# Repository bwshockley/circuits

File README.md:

# circuits
Collection of various circuit designs

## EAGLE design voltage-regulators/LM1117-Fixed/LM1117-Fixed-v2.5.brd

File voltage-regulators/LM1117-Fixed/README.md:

#LM1117 Based Fixed Voltage Regulator#

The goal behind this particular voltage regulator was a low drop-out (LDO) fairly high current (800mAh) accurate voltage regulator.  The LM1117 is an improvement over the LM317.  For additional information on the LM1117, please see Texas Instrument's [LM1117 Datasheet](http://www.ti.com/lit/ds/symlink/lm1117-n.pdf).

The board is designed with a 2.54mm (.1") pitch for headers at the bottom.  It can be installed vertically with a 90deg header or horizontally with a straight header.

R1 and LED are optional - only if you want to have a visual indicator that the LM1117 is providing power.

LM1117 is in SOT-223 package.

C1 and C2 should be 10uF+ Tantalum Capacitors in 7343 (metric) package.  See additional requirements in the datasheet.

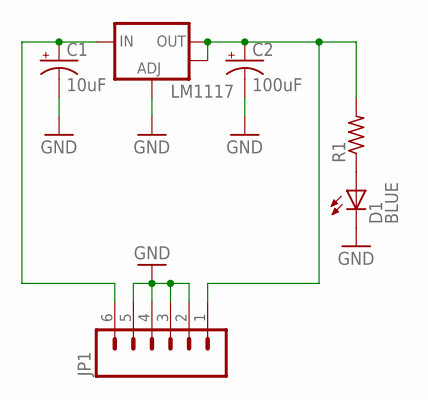
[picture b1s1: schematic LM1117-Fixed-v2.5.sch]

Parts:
C1: 10uF; CT7343
C2: 100uF; CT7343
D1: BLUE; CHIP-LED0805
JP1: M06NO_SILK_FEMALE_PTH; 1X06_NO_SILK
LM1117: V_REG_LM1117SOT223; SOT223
R1: R-US_R0805; R0805

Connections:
GND: C1.-, C2.-, D1.C, JP1.2, JP1.3, JP1.4, JP1.5, LM1117.1 (ADJ)
unnamed: C2.+, JP1.1, LM1117.2 (OUT), LM1117.4 (OUT), R1.2
unnamed: C1.+, JP1.6, LM1117.3 (IN)
unnamed: D1.A, R1.1

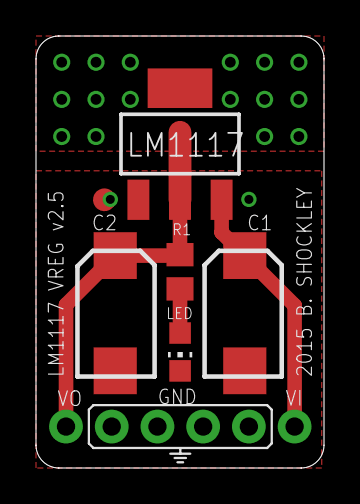
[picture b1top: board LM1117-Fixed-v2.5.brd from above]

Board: 2 copper layers, 16.0 x 24.0 mm, 6 parts (0 on the bottom side), 4 nets.

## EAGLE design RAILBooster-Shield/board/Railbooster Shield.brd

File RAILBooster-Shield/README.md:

#Railbooster Shield#

This design is based off of [RAILStars Railbooster](https://github.com/Railstars/RAILbooster).  It has been modified to fit onto an Arduino shield with a slightly different error check and control.

The shield should be good for DCC train control up to 12V and ~1.5Amps as is without heatsink.  Above that the LMD18200 will require some heatsink.  The voltage regulator is good as-is up to around 2Amps based off 15V input and 13V output.  The larger the deltaV between input and output voltage, the more likely a heatsink for the voltage regular will be required.  Please see the documentation on the voltage regulator.

The shield can provide voltage to the Arduino Uno R3 via the Vin pin of the Arduino.  It is fed off the shield voltage regulator.  In turn, the Arduino provides the 5V voltage for the shield's ATTINY, ICs, etc.

Adjust the output voltage of the voltage regulator with the adjustable resistor.

ATTINY44/84 can be programed via the Arudino UNO R3.

Design is provided as-is.  I cannot guarantee this will work and or not destroy your DCC trians.  Test the setup prior to powering the track.

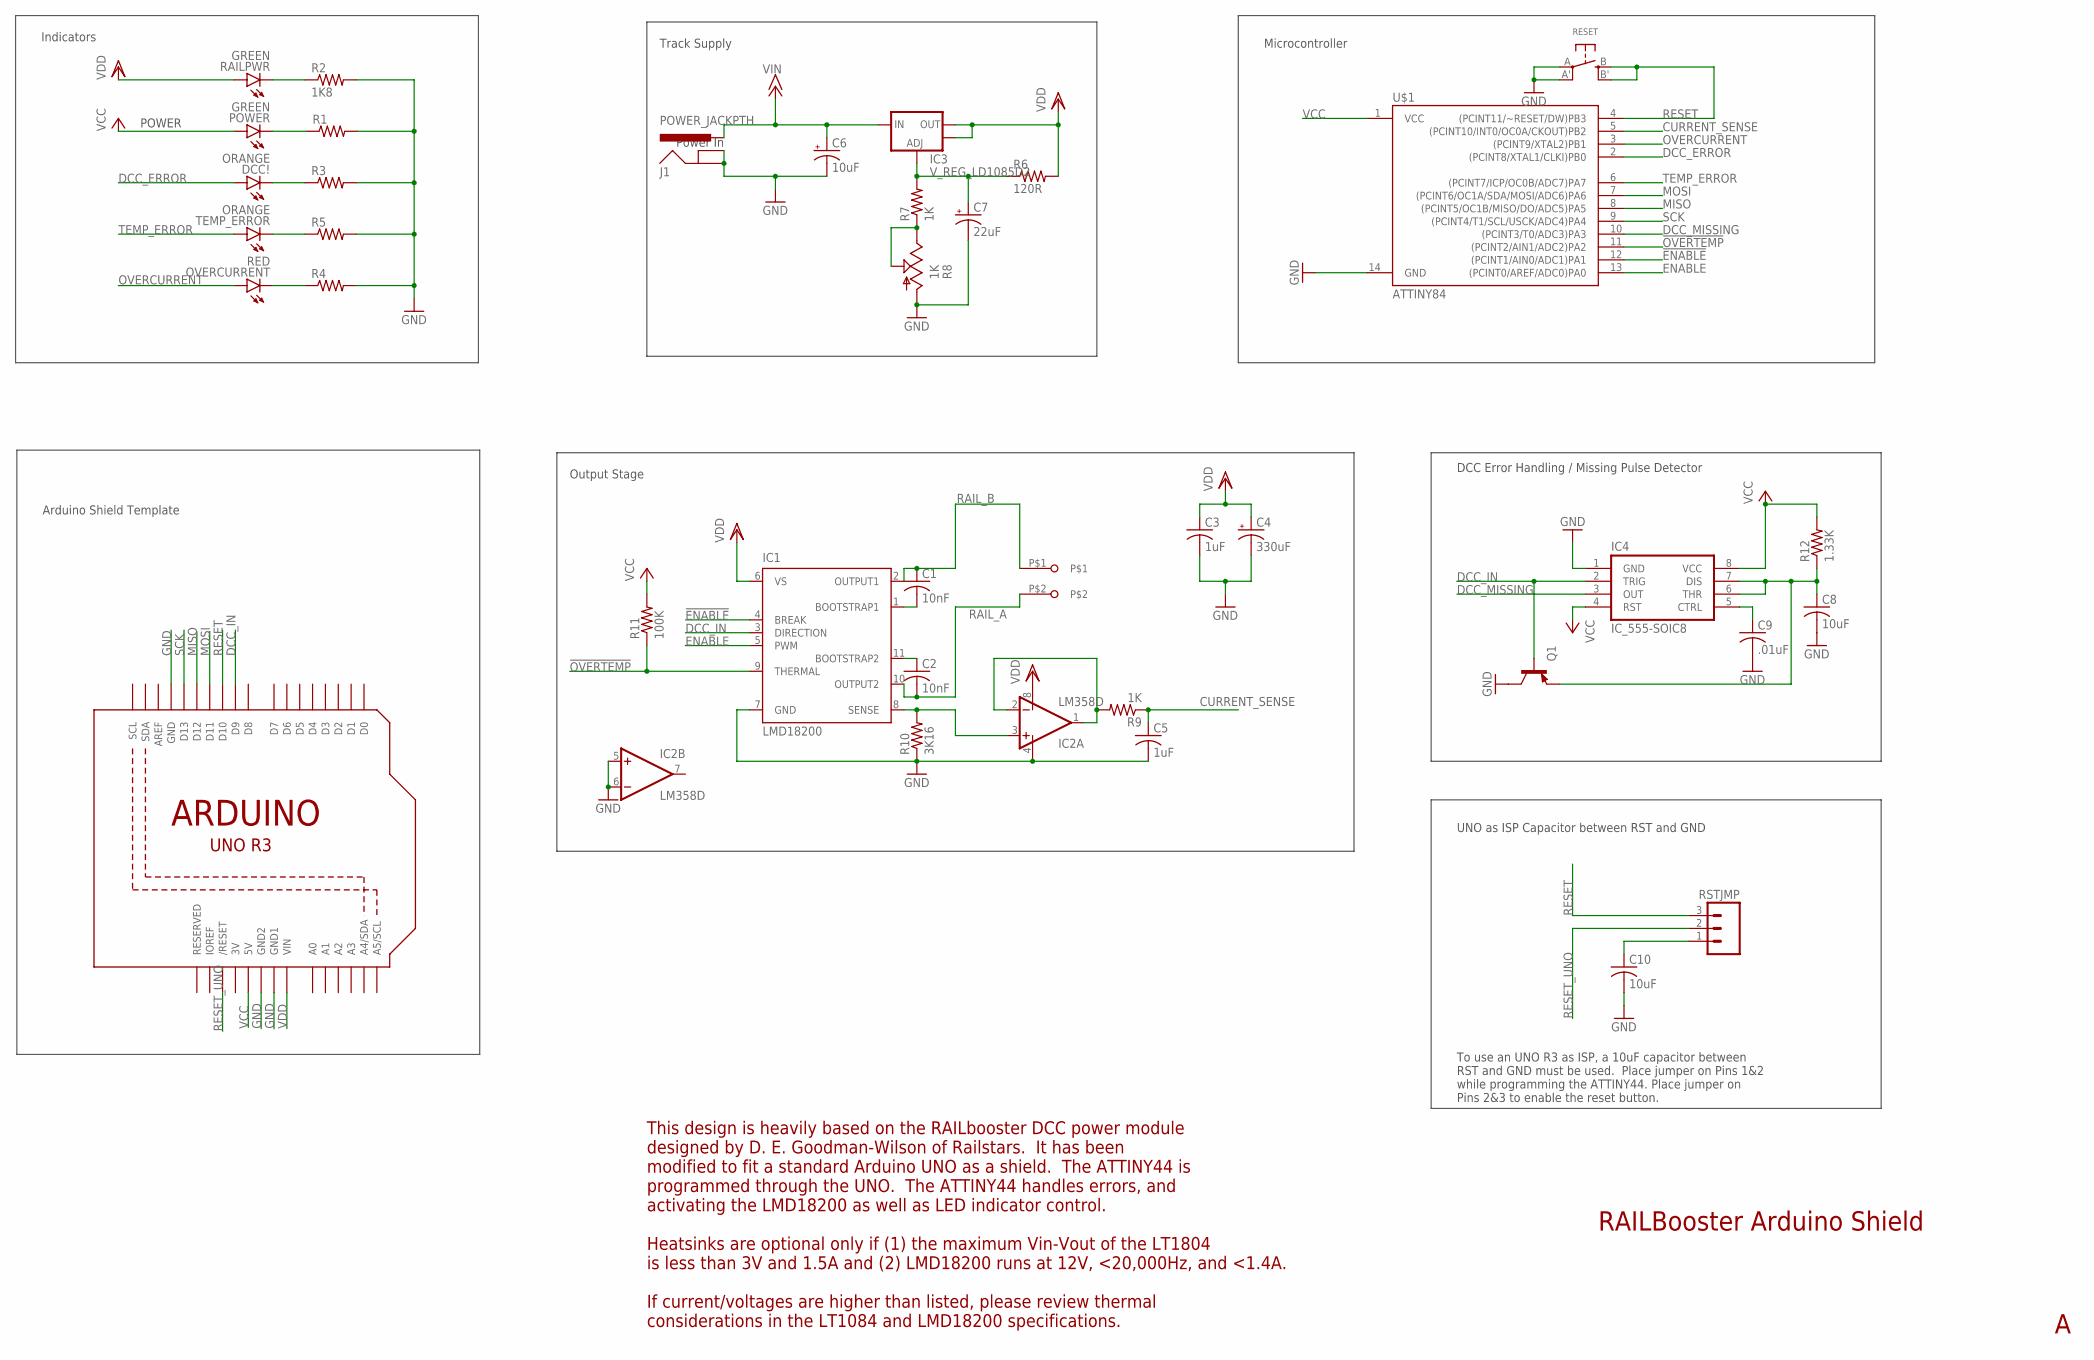
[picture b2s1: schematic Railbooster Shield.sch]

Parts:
C1, C2: 10nF; C1206
C3, C5: 1uF; C1206
C4: 330uF; E5-10,5
C6: 10uF; E2-5
C7: 22uF; E2-5
C8, C10: 10uF; C1206
C9: .01uF; C1206
DCC!: ORANGE; LED-1206
IC1: LMD18200; TO-220-11
IC2: LM358D; SO08
IC3: V_REG_LD1085D2; D2PACK/A
IC4: IC_555-SOIC8; SOIC-8
J1: POWER_JACKPTH; POWER_JACK_PTH
OVERCURRENT: RED; LED-1206
POWER: GREEN; LED-1206
Q1: TRANSISTOR_BJT_PNP-SOT-23-BCE; SOT-23
R1, R3, R4, R5: RESISTOR1206; 1206
R2: 1K8; 1206
R6: 120R; 1206
R7, R9: 1K; 1206
R8: 1K; S64W
R10: 3K16; 1206
R11: 100K; 1206
R12: 1.33K; 1206
RAILPWR: GREEN; LED-1206
RESET: SWITCH_TACT_SMT; EVQ-Q2
RSTJMP: M03PTH; 1X03
TEMP_ERROR: ORANGE; LED-1206
U1: ARDUINOR3-DIMENSION; ARDUINOR3
U$1: ATTINY84; SO14
X4: SCREWTERMINAL-5.08-2

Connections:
3V: U1.3V
!ENABLE: IC1.4 (BREAK), U$1.12 ((PCINT1/AIN0/ADC1)PA1)
!OVERTEMP: IC1.9 (THERMAL), R11.1, U$1.11 ((PCINT2/AIN1/ADC2)PA2)
CTRL: C9.1, IC4.5 (CTRL)
CURRENT_SENSE: C5.1, R9.1, U$1.5 ((PCINT10/INT0/OC0A/CKOUT)PB2)
CURRENT_SENSE_UNBUFFERED: IC2.1 (OUT), IC2.2 (-IN), R9.2
DCC_ERROR: DCC!.A, U$1.2 ((PCINT8/XTAL1/CLKI)PB0)
DCC_IN: IC1.3 (DIRECTION), IC4.2 (TRIG), Q1.1 (B), U1.D9
DCC_MISSING: IC4.3 (OUT), U$1.10 ((PCINT3/T0/ADC3)PA3)
ENABLE: IC1.5 (PWM), U$1.13 ((PCINT0/AREF/ADC0)PA0)
GND: C3.2, C4.-, C5.2, C6.-, C7.-, C8.2, C9.2, C10.2, IC1.7 (GND), IC2.4 (V-), IC2.5 (+IN), IC2.6 (-IN), IC4.1 (GND), J1.GND, J1.GNDBREAK, Q1.2 (C), R1.2, R2.2, R3.2, R4.2, R5.2, R8.A, R10.1, RESET.A, RESET.A' (P1), U1.GND, U1.GND1, U1.GND2, U$1.14 (GND)
MISO: U1.D12, U$1.8 ((PCINT5/OC1B/MISO/DO/ADC5)PA5)
MOSI: U1.D11, U$1.7 ((PCINT6/OC1A/SDA/MOSI/ADC6)PA6)
unnamed: R7.1, R8.E, R8.S
unnamed: C1.2, IC1.1 (BOOTSTRAP1)
unnamed: C2.1, IC1.11 (BOOTSTRAP2)
unnamed: IC1.8 (SENSE), IC2.3 (+IN), R10.2
unnamed: POWER.C, R1.1
unnamed: C7.+, IC3.1 (ADJ), R6.1, R7.2
unnamed: C10.1, RSTJMP.1
unnamed: DCC!.C, R3.1
unnamed: R5.1, TEMP_ERROR.C
unnamed: R2.1, RAILPWR.C
unnamed: C8.1, IC4.6 (THR), IC4.7 (DIS), Q1.3 (E), R12.1
unnamed: OVERCURRENT.C, R4.1
OVERCURRENT: OVERCURRENT.A, U$1.3 ((PCINT9/XTAL2)PB1)
RAIL_A: C2.2, IC1.10 (OUTPUT2), X4.P$2
RAIL_B: C1.1, IC1.2 (OUTPUT1), X4.P$1
RESET: RESET.B (S), RESET.B' (S1), RSTJMP.3, U1.D10, U$1.4 ((PCINT11/~RESET/DW)PB3)
RESET_UNO: RSTJMP.2, U1.RESET (/RESET)
SCK: U1.D13, U$1.9 ((PCINT4/T1/SCL/USCK/ADC4)PA4)
TEMP_ERROR: TEMP_ERROR.A, U$1.6 ((PCINT7/ICP/OC0B/ADC7)PA7)
VCC: IC4.4 (RST), IC4.8 (VCC), POWER.A, R11.2, R12.2, U1.5V, U$1.1 (VCC)
VDD: C3.1, C4.+, IC1.6 (VS), IC2.8 (V+), IC3.2 (OUT), IC3.TAB (OUT), R6.2, RAILPWR.A, U1.VIN
VIN: C6.+, IC3.3 (IN), J1.PWR

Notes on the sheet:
Track Supply
Power In
Indicators
Output Stage
POWER
Arduino Shield Template
RAILBooster Arduino Shield
This design is heavily based on the RAILbooster DCC power module designed by D. E. Goodman-Wilson of Railstars. It has been modified to fit a standard Arduino UNO as a shield. The ATTINY44 is programmed through the UNO. The ATTINY44 handles errors, and activating the LMD18200 as well as LED indicat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
Microcontroller
DCC Error Handling / Missing Pulse Detector
UNO as ISP Capacitor between RST and GND
To use an UNO R3 as ISP, a 10uF capacitor between RST and GND must be used. Place jumper on Pins 1&2 while programming the ATTINY44. Place jumper on Pins 2&3 to enable the reset button.

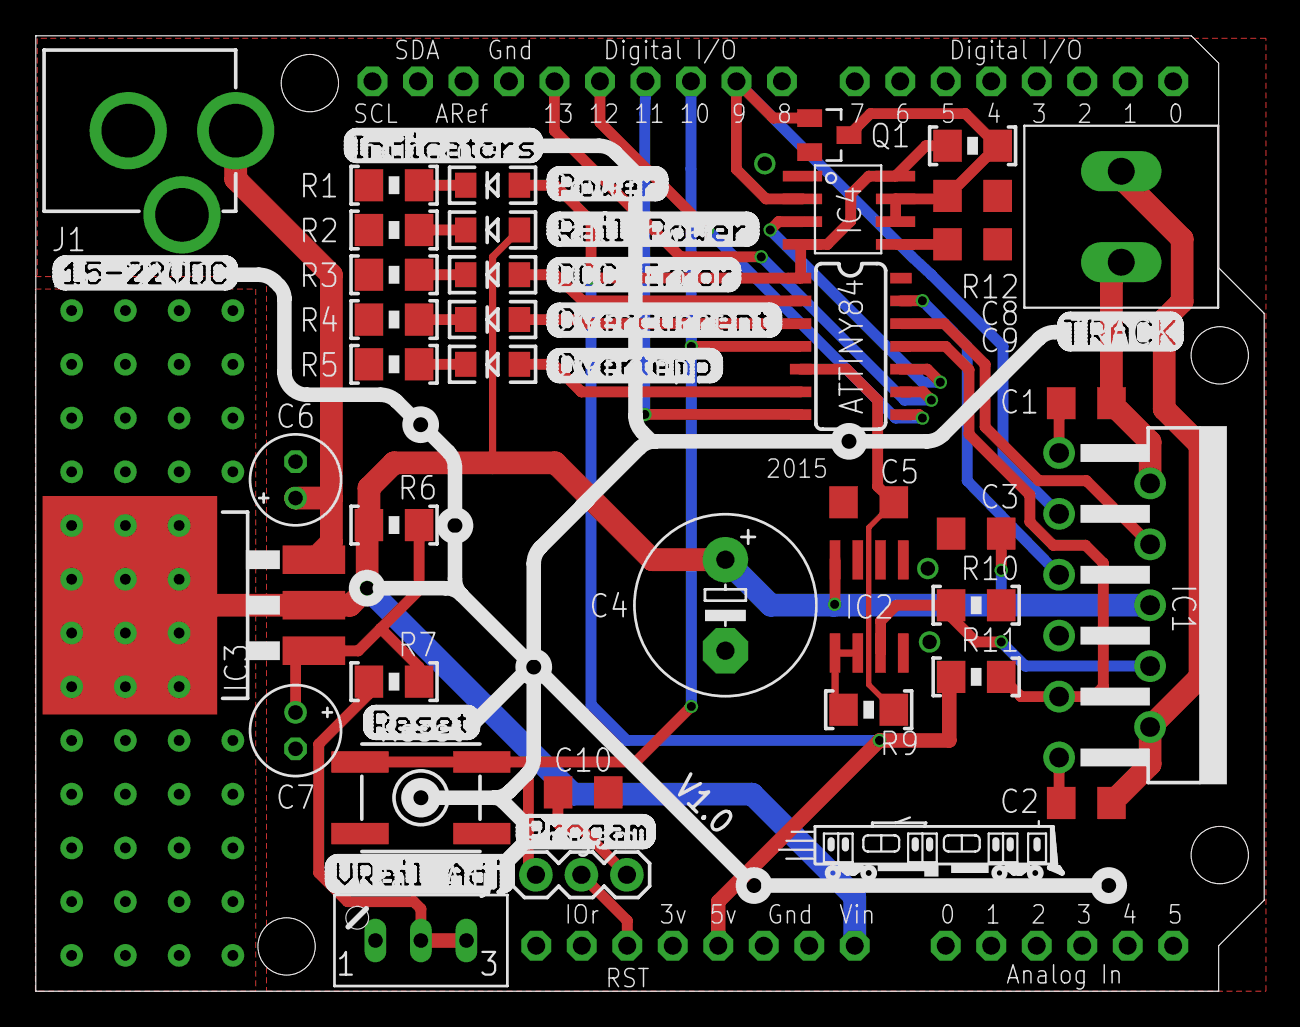
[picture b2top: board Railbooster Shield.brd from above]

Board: 2 copper layers, 68.6 x 53.3 mm, 38 parts (0 on the bottom side), 34 nets.

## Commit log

2015-09-25 Rename READ.me to README.md
2015-09-25 Update Railbooster Shield BOM.txt
    Added major components to list - R/C are not set yet.
2015-09-25 Added details about the board and setup
2015-09-25 Update to remove rouge connector
2015-09-25 Create READ
2015-09-25 Rename READ to README.md
2015-09-28 Rename GPIO_Board_v2.1 to GPIO_Board_v2.1.brd

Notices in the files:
parts and their libraries:
SparkFun-PowerIC: Licensing: Creative Commons ShareAlike 4.0 International - https://creativecommons.org/licenses/by-sa/4.0
microbuilder: This work is placed in the public domain, and may be freely used for commercial and non-commercial work with the following conditions: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
